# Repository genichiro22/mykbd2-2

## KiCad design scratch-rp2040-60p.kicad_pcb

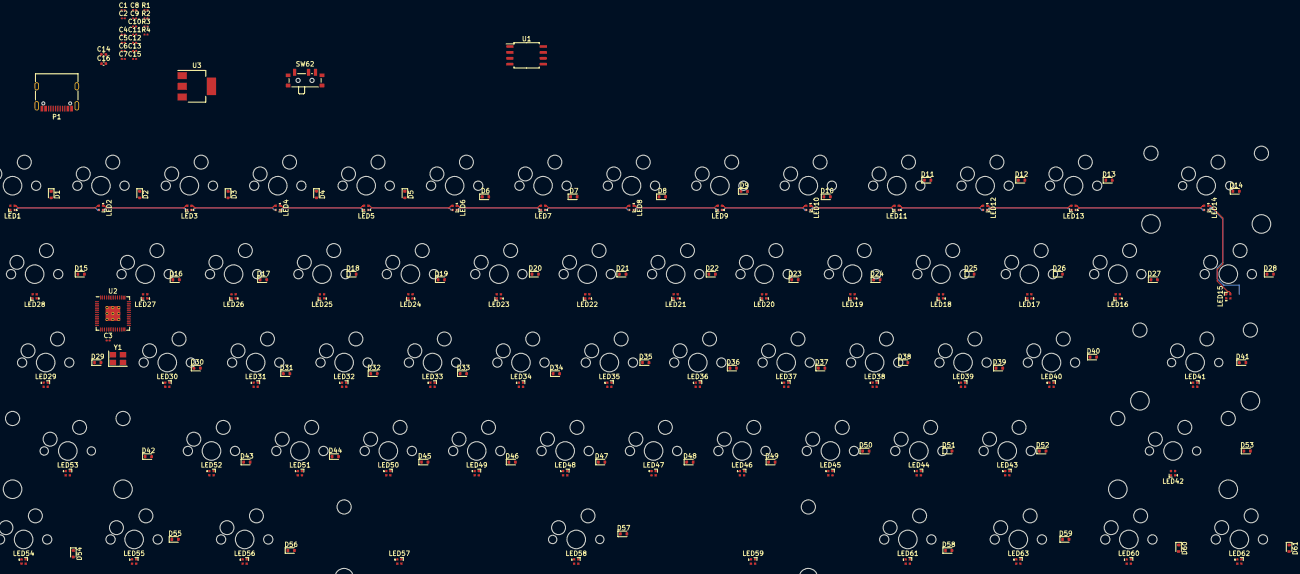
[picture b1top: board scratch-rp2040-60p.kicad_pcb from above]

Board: 2 copper layers, 211 parts (0 on the bottom side), 162 nets.

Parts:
C1, C4, C5, C7, C9, C10, C11, C12, C13, C15: 100n; C_0201_0603Metric
C2, C3: 27p; C_0201_0603Metric
C6, C8: 1u; C_0201_0603Metric
C14, C16: 10u; C_0402_1005Metric
D1, D2, D3, D4, D5, D6, D7, D8, D9, D10, D11, D12, D13, D14, D15, D16, D17, D18, D19, D20, D21, D22, D23, D24, D25, D26, D27, D28, D29, D30, D31, D32, D33, D34, D35, D36, D37, D38, D39, D40, D41, D42, D43, D44, D45, D46, D47, D48, D49, D50, D51, D52, D53, D54, D55, D56, D57, D58, D59, D60, D61: 1N4148W; D_SOD-523
LED1, LED2, LED3, LED4, LED5, LED6, LED7, LED8, LED9, LED10, LED11, LED12, LED13, LED14, LED15, LED16, LED17, LED18, LED19, LED20, LED21, LED22, LED23, LED24, LED25, LED26, LED27, LED28, LED29, LED30, LED31, LED32, LED33, LED34, LED35, LED36, LED37, LED38, LED39, LED40, LED41, LED42, LED43, LED44, LED45, LED46, LED47, LED48, LED49, LED50, LED51, LED52, LED53, LED54, LED55, LED56, LED57, LED58, LED59, LED60, LED61, LED62, LED63: LED_SK6812MINI-E; LED_SK6812_EC15_1.5x1.5mm
P1: USB_C_Plug_USB2.0; USB_C_Receptacle_G-Switch_GT-USB-7010ASV
R1: 1k; R_0201_0603Metric
R2, R3: 27.4; R_0201_0603Metric
R4: 5.1k; R_0201_0603Metric
SW1, SW2, SW3, SW4, SW5, SW6, SW7, SW8, SW9, SW10, SW11, SW12, SW13, SW16, SW17, SW18, SW19, SW20, SW21, SW22, SW23, SW24, SW25, SW26, SW27, SW30, SW31, SW32, SW33, SW34, SW35, SW36, SW37, SW38, SW39, SW40, SW43, SW44, SW45, SW46, SW47, SW48, SW49, SW50, SW51, SW52: SW_Push; CherryMX_Hotswap_1u
SW14: SW_Push; CherryMX_Hotswap_2u
SW15, SW28: SW_Push; CherryMX_Hotswap_1.5u
SW29: SW_Push; CherryMX_Hotswap_1.75u
SW41, SW42: SW_Push; CherryMX_Hotswap_2.25u
SW53: SW_Push; CherryMX_Hotswap_2.75u
SW54, SW55, SW56, SW58, SW59, SW60, SW61: SW_Push; CherryMX_Hotswap_1.25u
SW57: SW_Push; CherryMX_Hotswap_6.25u
SW62: SW_SPST; SW_SPDT_PCM12
U1: W25Q128JVS; SOIC-8_5.23x5.23mm_P1.27mm
U2: RP2040; RP2040-QFN-56
U3: NCP1117-3.3_SOT223; SOT-223-3_TabPin2
Y1: 12MHz; Crystal_SMD_3225-4Pin_3.2x2.5mm

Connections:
+1V1: C4.1, C5.1, C6.1, U2.23 (DVDD), U2.45 (VREG_VOUT), U2.50 (DVDD)
+3.3V: C1.1, C7.1, C8.1, C9.1, C10.1, C11.1, C12.1, C13.1, C15.1, C16.1, LED1.4 (VDD), LED2.4 (VDD), LED3.4 (VDD), LED4.4 (VDD), LED5.4 (VDD), LED6.4 (VDD), LED7.4 (VDD), LED8.4 (VDD), LED9.4 (VDD), LED10.4 (VDD), LED11.4 (VDD), LED12.4 (VDD), LED13.4 (VDD), LED14.4 (VDD), LED15.4 (VDD), LED16.4 (VDD), LED17.4 (VDD), LED18.4 (VDD), LED19.4 (VDD), LED20.4 (VDD), LED21.4 (VDD), LED22.4 (VDD), LED23.4 (VDD), LED24.4 (VDD), LED25.4 (VDD), LED26.4 (VDD), LED27.4 (VDD), LED28.4 (VDD), LED29.4 (VDD), LED30.4 (VDD), LED31.4 (VDD), LED32.4 (VDD), LED33.4 (VDD), LED34.4 (VDD), LED35.4 (VDD), LED36.4 (VDD), LED37.4 (VDD), LED38.4 (VDD), LED39.4 (VDD), LED40.4 (VDD), LED41.4 (VDD), LED42.4 (VDD), LED43.4 (VDD), LED44.4 (VDD), LED45.4 (VDD), LED46.4 (VDD), LED47.4 (VDD), LED48.4 (VDD), LED49.4 (VDD), LED50.4 (VDD), LED51.4 (VDD), LED52.4 (VDD), LED53.4 (VDD), LED54.4 (VDD), LED55.4 (VDD), LED56.4 (VDD), LED57.4 (VDD), LED58.4 (VDD), LED59.4 (VDD), LED60.4 (VDD), LED61.4 (VDD), LED62.4 (VDD), LED63.4 (VDD), U1.8 (VCC), U2.1 (IOVDD), U2.10 (IOVDD), U2.22 (IOVDD), U2.33 (IOVDD), U2.42 (IOVDD), U2.43 (ADC_AVDD), U2.44 (VREG_IN), U2.48 (USB_VDD), U2.49 (IOVDD), U3.2 (VO)
COL1: SW1.1, SW15.1, SW29.1, SW42.1, SW54.1, U2.3 (GPIO1)
COL2: SW2.1, SW16.1, SW30.1, SW43.1, SW55.1, U2.4 (GPIO2)
COL3: SW3.1, SW17.1, SW31.1, SW44.1, SW56.1, U2.5 (GPIO3)
COL4: SW4.1, SW18.1, SW32.1, SW45.1, SW57.1, U2.6 (GPIO4)
COL5: SW5.1, SW19.1, SW33.1, SW46.1, SW58.1, U2.7 (GPIO5)
COL6: SW6.1, SW20.1, SW34.1, SW47.1, SW59.1, U2.8 (GPIO6)
COL7: SW7.1, SW21.1, SW35.1, SW48.1, SW60.1, U2.9 (GPIO7)
COL8: SW8.1, SW22.1, SW36.1, SW49.1, SW61.1, U2.11 (GPIO8)
COL9: SW9.1, SW23.1, SW37.1, SW50.1, U2.12 (GPIO9)
COL10: SW10.1, SW24.1, SW38.1, SW51.1, U2.13 (GPIO10)
COL11: SW11.1, SW25.1, SW39.1, SW52.1, U2.14 (GPIO11)
COL12: SW12.1, SW26.1, SW40.1, SW53.1, U2.15 (GPIO12)
COL13: SW13.1, SW27.1, SW41.1, U2.16 (GPIO13)
COL14: SW14.1, SW28.1, U2.17 (GPIO14)
GND: C1.2, C2.1, C3.1, C4.2, C5.2, C6.2, C7.2, C8.2, C9.2, C10.2, C11.2, C12.2, C13.2, C14.2, C15.2, C16.2, LED1.2 (VSS), LED2.2 (VSS), LED3.2 (VSS), LED4.2 (VSS), LED5.2 (VSS), LED6.2 (VSS), LED7.2 (VSS), LED8.2 (VSS), LED9.2 (VSS), LED10.2 (VSS), LED11.2 (VSS), LED12.2 (VSS), LED13.2 (VSS), LED14.2 (VSS), LED15.2 (VSS), LED16.2 (VSS), LED17.2 (VSS), LED18.2 (VSS), LED19.2 (VSS), LED20.2 (VSS), LED21.2 (VSS), LED22.2 (VSS), LED23.2 (VSS), LED24.2 (VSS), LED25.2 (VSS), LED26.2 (VSS), LED27.2 (VSS), LED28.2 (VSS), LED29.2 (VSS), LED30.2 (VSS), LED31.2 (VSS), LED32.2 (VSS), LED33.2 (VSS), LED34.2 (VSS), LED35.2 (VSS), LED36.2 (VSS), LED37.2 (VSS), LED38.2 (VSS), LED39.2 (VSS), LED40.2 (VSS), LED41.2 (VSS), LED42.2 (VSS), LED43.2 (VSS), LED44.2 (VSS), LED45.2 (VSS), LED46.2 (VSS), LED47.2 (VSS), LED48.2 (VSS), LED49.2 (VSS), LED50.2 (VSS), LED51.2 (VSS), LED52.2 (VSS), LED53.2 (VSS), LED54.2 (VSS), LED55.2 (VSS), LED56.2 (VSS), LED57.2 (VSS), LED58.2 (VSS), LED59.2 (VSS), LED60.2 (VSS), LED61.2 (VSS), LED62.2 (VSS), LED63.2 (VSS), P1.A1 (GND), P1.A12 (GND), P1.B1 (GND), P1.B12 (GND), P1.S1 (SHIELD), R4.2, SW62.1 (A), U1.4 (GND), U2.19 (TESTEN), U2.57 (GND), U3.1 (GND), Y1.2, Y1.4
LED_IN: LED1.3 (DIN), U2.38 (GPIO26_ADC0)
LED_OUT: LED63.1 (DOUT), U2.39 (GPIO27_ADC1)
unnamed: D1.1 (K), SW1.2
unnamed: D2.1 (K), SW2.2
unnamed: D3.1 (K), SW3.2
unnamed: D4.1 (K), SW4.2
unnamed: D5.1 (K), SW5.2
unnamed: D6.1 (K), SW6.2
unnamed: D7.1 (K), SW7.2
unnamed: D8.1 (K), SW8.2
unnamed: D9.1 (K), SW9.2
unnamed: D10.1 (K), SW10.2
unnamed: D11.1 (K), SW11.2
unnamed: D12.1 (K), SW12.2
unnamed: D13.1 (K), SW13.2
unnamed: D14.1 (K), SW14.2
unnamed: D15.1 (K), SW15.2
unnamed: D16.1 (K), SW16.2
unnamed: D17.1 (K), SW17.2
unnamed: D18.1 (K), SW18.2
unnamed: D19.1 (K), SW19.2
unnamed: D20.1 (K), SW20.2
unnamed: D21.1 (K), SW21.2
unnamed: D22.1 (K), SW22.2
unnamed: D23.1 (K), SW23.2
unnamed: D24.1 (K), SW24.2
unnamed: D25.1 (K), SW25.2
unnamed: D26.1 (K), SW26.2
unnamed: D27.1 (K), SW27.2
unnamed: D28.1 (K), SW28.2
unnamed: D29.1 (K), SW29.2
unnamed: D30.1 (K), SW30.2
unnamed: D31.1 (K), SW31.2
unnamed: D32.1 (K), SW32.2
unnamed: D33.1 (K), SW33.2
unnamed: D34.1 (K), SW34.2
unnamed: D35.1 (K), SW35.2
unnamed: D36.1 (K), SW36.2
unnamed: D37.1 (K), SW37.2
unnamed: D38.1 (K), SW38.2
unnamed: D39.1 (K), SW39.2
unnamed: D40.1 (K), SW40.2
unnamed: D41.1 (K), SW41.2
unnamed: D42.1 (K), SW42.2
unnamed: D43.1 (K), SW43.2
unnamed: D44.1 (K), SW44.2
unnamed: D45.1 (K), SW45.2
unnamed: D46.1 (K), SW46.2
unnamed: D47.1 (K), SW47.2
unnamed: D48.1 (K), SW48.2
unnamed: D49.1 (K), SW49.2
unnamed: D50.1 (K), SW50.2
unnamed: D51.1 (K), SW51.2
unnamed: D52.1 (K), SW52.2
unnamed: D53.1 (K), SW53.2
unnamed: D54.1 (K), SW54.2
unnamed: D55.1 (K), SW55.2
unnamed: D56.1 (K), SW56.2
unnamed: D57.1 (K), SW57.2
unnamed: D58.1 (K), SW58.2
unnamed: D59.1 (K), SW59.2
unnamed: D60.1 (K), SW60.2
unnamed: D61.1 (K), SW61.2
unnamed: LED1.1 (DOUT), LED2.3 (DIN)
unnamed: LED2.1 (DOUT), LED3.3 (DIN)
unnamed: LED3.1 (DOUT), LED4.3 (DIN)
unnamed: LED4.1 (DOUT), LED5.3 (DIN)
unnamed: LED5.1 (DOUT), LED6.3 (DIN)
unnamed: LED6.1 (DOUT), LED7.3 (DIN)
unnamed: LED7.1 (DOUT), LED8.3 (DIN)
unnamed: LED8.1 (DOUT), LED9.3 (DIN)
unnamed: LED9.1 (DOUT), LED10.3 (DIN)
unnamed: LED10.1 (DOUT), LED11.3 (DIN)
unnamed: LED11.1 (DOUT), LED12.3 (DIN)
unnamed: LED12.1 (DOUT), LED13.3 (DIN)
unnamed: LED13.1 (DOUT), LED14.3 (DIN)
unnamed: LED14.1 (DOUT), LED15.3 (DIN)
unnamed: LED15.1 (DOUT), LED16.3 (DIN)
unnamed: LED16.1 (DOUT), LED17.3 (DIN)
unnamed: LED17.1 (DOUT), LED18.3 (DIN)
unnamed: LED18.1 (DOUT), LED19.3 (DIN)
unnamed: LED19.1 (DOUT), LED20.3 (DIN)
unnamed: LED20.1 (DOUT), LED21.3 (DIN)
unnamed: LED21.1 (DOUT), LED22.3 (DIN)
unnamed: LED22.1 (DOUT), LED23.3 (DIN)
unnamed: LED23.1 (DOUT), LED24.3 (DIN)
unnamed: LED24.1 (DOUT), LED25.3 (DIN)
unnamed: LED25.1 (DOUT), LED26.3 (DIN)
unnamed: LED26.1 (DOUT), LED27.3 (DIN)
unnamed: LED27.1 (DOUT), LED28.3 (DIN)
unnamed: LED28.1 (DOUT), LED29.3 (DIN)
unnamed: LED29.1 (DOUT), LED30.3 (DIN)
unnamed: LED30.1 (DOUT), LED31.3 (DIN)
unnamed: LED31.1 (DOUT), LED32.3 (DIN)
unnamed: LED32.1 (DOUT), LED33.3 (DIN)
unnamed: LED33.1 (DOUT), LED34.3 (DIN)
unnamed: LED34.1 (DOUT), LED35.3 (DIN)
unnamed: LED35.1 (DOUT), LED36.3 (DIN)
unnamed: LED36.1 (DOUT), LED37.3 (DIN)
unnamed: LED37.1 (DOUT), LED38.3 (DIN)
unnamed: LED38.1 (DOUT), LED39.3 (DIN)
unnamed: LED39.1 (DOUT), LED40.3 (DIN)
unnamed: LED40.1 (DOUT), LED41.3 (DIN)
unnamed: LED41.1 (DOUT), LED42.3 (DIN)
unnamed: LED42.1 (DOUT), LED43.3 (DIN)
unnamed: LED43.1 (DOUT), LED44.3 (DIN)
unnamed: LED44.1 (DOUT), LED45.3 (DIN)
unnamed: LED45.1 (DOUT), LED46.3 (DIN)
unnamed: LED46.1 (DOUT), LED47.3 (DIN)
unnamed: LED47.1 (DOUT), LED48.3 (DIN)
unnamed: LED48.1 (DOUT), LED49.3 (DIN)
unnamed: LED49.1 (DOUT), LED50.3 (DIN)
unnamed: LED50.1 (DOUT), LED51.3 (DIN)
unnamed: LED51.1 (DOUT), LED52.3 (DIN)
unnamed: LED52.1 (DOUT), LED53.3 (DIN)
unnamed: LED53.1 (DOUT), LED54.3 (DIN)
unnamed: LED54.1 (DOUT), LED55.3 (DIN)
unnamed: LED55.1 (DOUT), LED56.3 (DIN)
unnamed: LED56.1 (DOUT), LED57.3 (DIN)
unnamed: LED57.1 (DOUT), LED58.3 (DIN)
unnamed: LED58.1 (DOUT), LED59.3 (DIN)
unnamed: LED59.1 (DOUT), LED60.3 (DIN)
unnamed: LED60.1 (DOUT), LED61.3 (DIN)
unnamed: LED61.1 (DOUT), LED62.3 (DIN)
unnamed: LED62.1 (DOUT), LED63.3 (DIN)
unnamed: P1.A5 (CC), R4.1
unnamed: R1.1, SW62.2 (B)
unnamed: U1.6 (CLK), U2.52 (QSPI_SCLK)
unnamed: U1.5 (DI(IO0)), U2.53 (QSPI_SD0)
unnamed: U1.2 (DO(IO1)), U2.55 (QSPI_SD1)
unnamed: U1.3 (IO2), U2.54 (QSPI_SD2)
unnamed: U1.7 (IO3), U2.51 (QSPI_SD3)
unnamed: R1.2, U1.1 (~CS), U2.56 (QSPI_SS)
unnamed: R3.1, U2.46 (USB_DM)
unnamed: R2.1, U2.47 (USB_DP)
unnamed: C2.2, U2.20 (XIN), Y1.3
unnamed: C3.2, U2.21 (XOUT), Y1.1
ROW1: D1.2 (A), D2.2 (A), D3.2 (A), D4.2 (A), D5.2 (A), D6.2 (A), D7.2 (A), D8.2 (A), D9.2 (A), D10.2 (A), D11.2 (A), D12.2 (A), D13.2 (A), D14.2 (A), U2.18 (GPIO15)
ROW2: D15.2 (A), D16.2 (A), D17.2 (A), D18.2 (A), D19.2 (A), D20.2 (A), D21.2 (A), D22.2 (A), D23.2 (A), D24.2 (A), D25.2 (A), D26.2 (A), D27.2 (A), D28.2 (A), U2.27 (GPIO16)
ROW3: D29.2 (A), D30.2 (A), D31.2 (A), D32.2 (A), D33.2 (A), D34.2 (A), D35.2 (A), D36.2 (A), D37.2 (A), D38.2 (A), D39.2 (A), D40.2 (A), D41.2 (A), U2.28 (GPIO17)
ROW4: D42.2 (A), D43.2 (A), D44.2 (A), D45.2 (A), D46.2 (A), D47.2 (A), D48.2 (A), D49.2 (A), D50.2 (A), D51.2 (A), D52.2 (A), D53.2 (A), U2.29 (GPIO18)
ROW5: D54.2 (A), D55.2 (A), D56.2 (A), D57.2 (A), D58.2 (A), D59.2 (A), D60.2 (A), D61.2 (A), U2.30 (GPIO19)
USB_D+: P1.A6 (D+), R2.2
USB_D-: P1.A7 (D-), R3.2
VBUS: C14.1, P1.A4 (VBUS), P1.A9 (VBUS), P1.B4 (VBUS), P1.B9 (VBUS), U3.3 (VI)

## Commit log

2023-09-22 added first key and SK6812mini-e
2023-09-22 footprint assigned
2023-09-22 20230922 end
